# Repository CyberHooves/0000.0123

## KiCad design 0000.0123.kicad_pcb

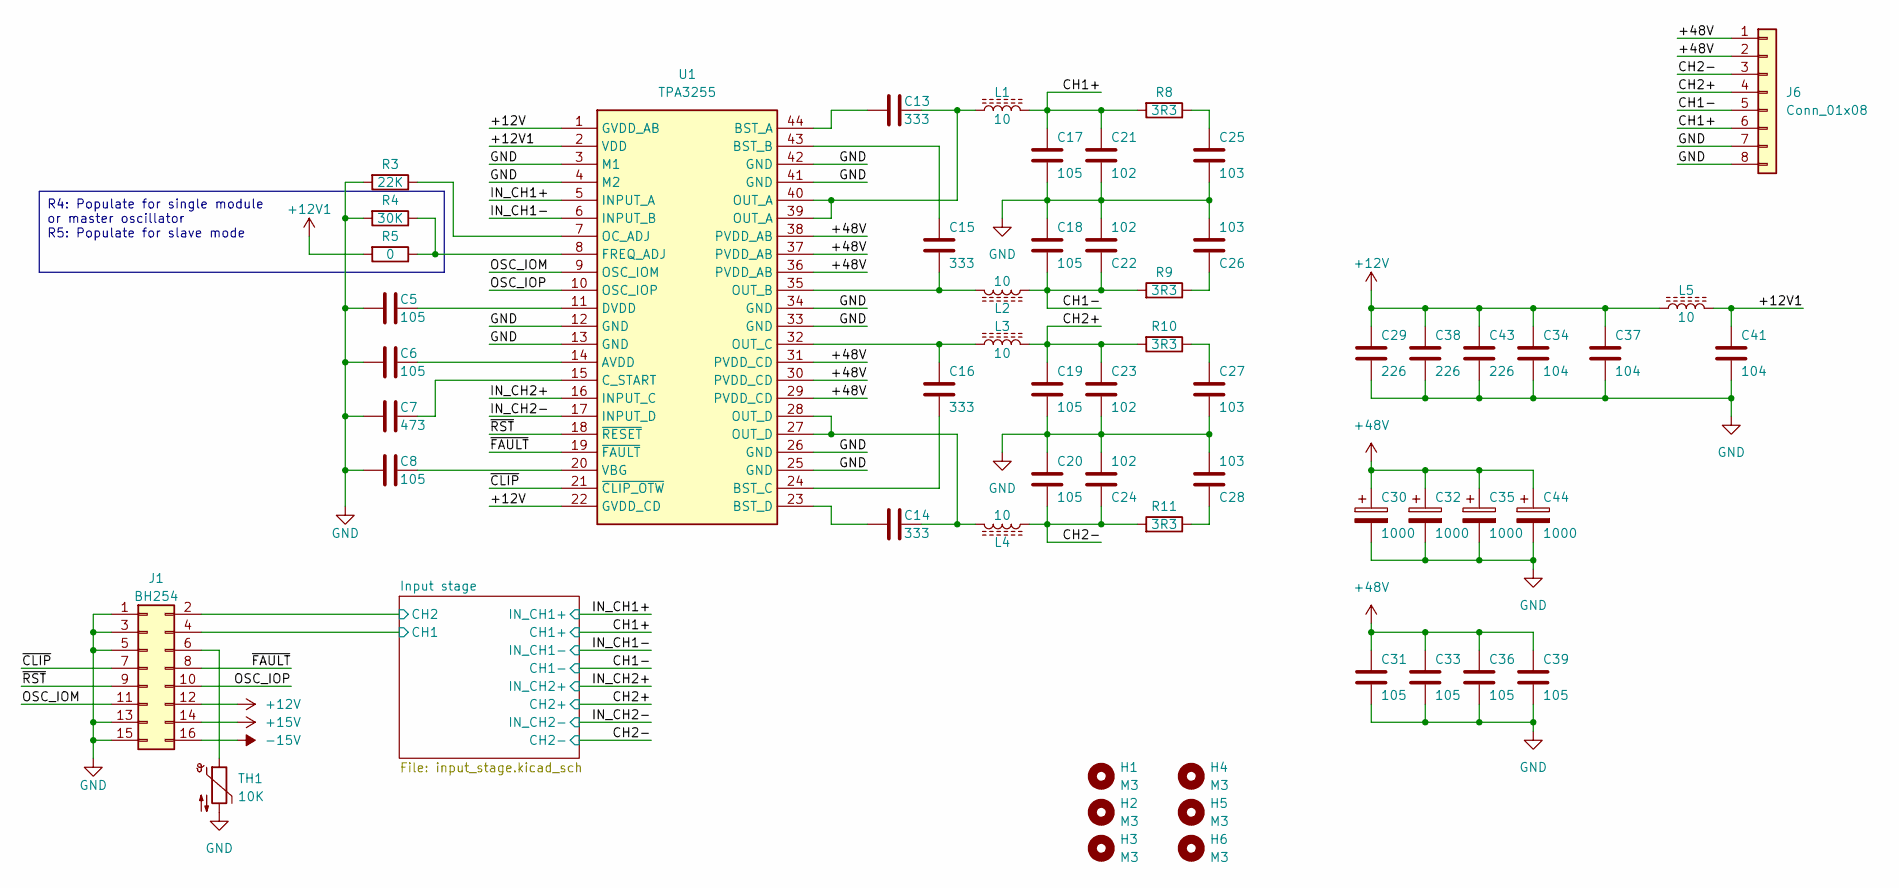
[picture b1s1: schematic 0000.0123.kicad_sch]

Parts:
C5, C6, C8: 105; C_0805_2012Metric
C7: 473; C_0805_2012Metric
C13, C14, C15, C16: 333; C_0805_2012Metric
C17, C18, C19, C20: 105; C_Rect_L18.0mm_W8.0mm_P15.00mm_FKS3_FKP3
C21, C22, C23, C24: 102; C_0805_2012Metric
C25, C26, C27, C28: 103; C_0805_2012Metric
C29, C38, C43: 226; C_1210_3225Metric
C30, C32, C35, C44: 1000; CP_Radial_D16.0mm_P7.50mm
C31, C33, C36, C39: 105; C_1210_3225Metric
C34, C37, C41: 104; C_0805_2012Metric
H1, H2, H3, H4, H5, H6: M3; MountingHole_3.2mm_M3
J1: BH254; IDC-Header_2x08_P2.54mm_Vertical
J6: Conn_01x08; PhoenixContact_MCV_1,5_8-G-5.08_1x08_P5.08mm_Vertical
L1, L2, L3, L4: 10; L_TOROID_D25_W10_P8_V_1
L5: 10; L_1210_3225Metric
R3: 22K; R_0805_2012Metric
R4: 30K; R_0805_2012Metric
R5: 0; R_0805_2012Metric
R8, R9, R10, R11: 3R3; R_0805_2012Metric
TH1: 10K; R_0805_2012Metric
U1: TPA3255; HTSSOP-44_6.1x14mm_P0.635mm_TopEP4.14x7.01mm

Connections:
+12V: C29.1, C34.1, C37.1, C38.1, C43.1, J1.12, L5.1, U1.1 (GVDD_AB), U1.22 (GVDD_CD)
+12V1: C41.1, L5.2, R5.2, U1.2 (VDD)
+15V: J1.14; also elsewhere on the board
+48V: C30.1, C31.1, C32.1, C33.1, C35.1, C36.1, C39.1, C44.1, J6.1, J6.2, U1.29 (PVDD_CD), U1.30 (PVDD_CD), U1.31 (PVDD_CD), U1.36 (PVDD_AB), U1.37 (PVDD_AB), U1.38 (PVDD_AB)
-15V: J1.16; also elsewhere on the board
/CH1+: C17.1, C21.1, J6.6, L1.2, R8.2; also elsewhere on the board
/CH1-: C18.2, C22.1, J6.5, L2.2, R9.2; also elsewhere on the board
/CH2+: C19.1, C23.1, J6.4, L3.2, R10.2; also elsewhere on the board
/CH2-: C20.2, C24.1, J6.3, L4.2, R11.2; also elsewhere on the board
/IN_CH1+: U1.5 (INPUT_A); also elsewhere on the board
/IN_CH1-: U1.6 (INPUT_B); also elsewhere on the board
/IN_CH2+: U1.16 (INPUT_C); also elsewhere on the board
/IN_CH2-: U1.17 (INPUT_D); also elsewhere on the board
/Input stage/CH1: J1.4; also elsewhere on the board
/Input stage/CH2: J1.2; also elsewhere on the board
/OSC_IOM: J1.11, U1.9 (OSC_IOM)
/OSC_IOP: J1.10, U1.10 (OSC_IOP)
/~CLIP: J1.7, U1.21 (~CLIP_OTW)
/~FAULT: J1.8, U1.19 (~FAULT)
/~RST: J1.9, U1.18 (~RESET)
GND: C5.1, C6.1, C7.1, C8.1, C17.2, C18.1, C19.2, C20.1, C21.2, C22.2, C23.2, C24.2, C25.2, C26.2, C27.2, C28.2, C29.2, C30.2, C31.2, C32.2, C33.2, C34.2, C35.2, C36.2, C37.2, C38.2, C39.2, C41.2, C43.2, C44.2, J1.1, J1.3, J1.5, J1.13, J1.15, J6.7, J6.8, R3.2, R4.2, TH1.2, U1.3 (M1), U1.4 (M2), U1.12 (GND), U1.13 (GND), U1.25 (GND), U1.26 (GND), U1.33 (GND), U1.34 (GND), U1.41 (GND), U1.42 (GND); also elsewhere on the board
unnamed: C13.2, L1.1, U1.39 (OUT_A), U1.40 (OUT_A)
unnamed: C14.2, L4.1, U1.27 (OUT_D), U1.28 (OUT_D)
unnamed: C25.1, R8.1
unnamed: C26.1, R9.1
unnamed: C27.1, R10.1
unnamed: C28.1, R11.1
unnamed: J1.6, TH1.1
unnamed: C6.2, U1.14 (AVDD)
unnamed: C13.1, U1.44 (BST_A)
unnamed: C15.1, U1.43 (BST_B)
unnamed: C16.2, U1.24 (BST_C)
unnamed: C14.1, U1.23 (BST_D)
unnamed: C7.2, U1.15 (C_START)
unnamed: C5.2, U1.11 (DVDD)
unnamed: R4.1, R5.1, U1.8 (FREQ_ADJ)
unnamed: R3.1, U1.7 (OC_ADJ)
unnamed: C15.2, L2.1, U1.35 (OUT_B)
unnamed: C16.1, L3.1, U1.32 (OUT_C)
unnamed: C8.2, U1.20 (VBG)

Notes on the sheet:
R4: Populate for single module or master oscillator R5: Populate for slave mode

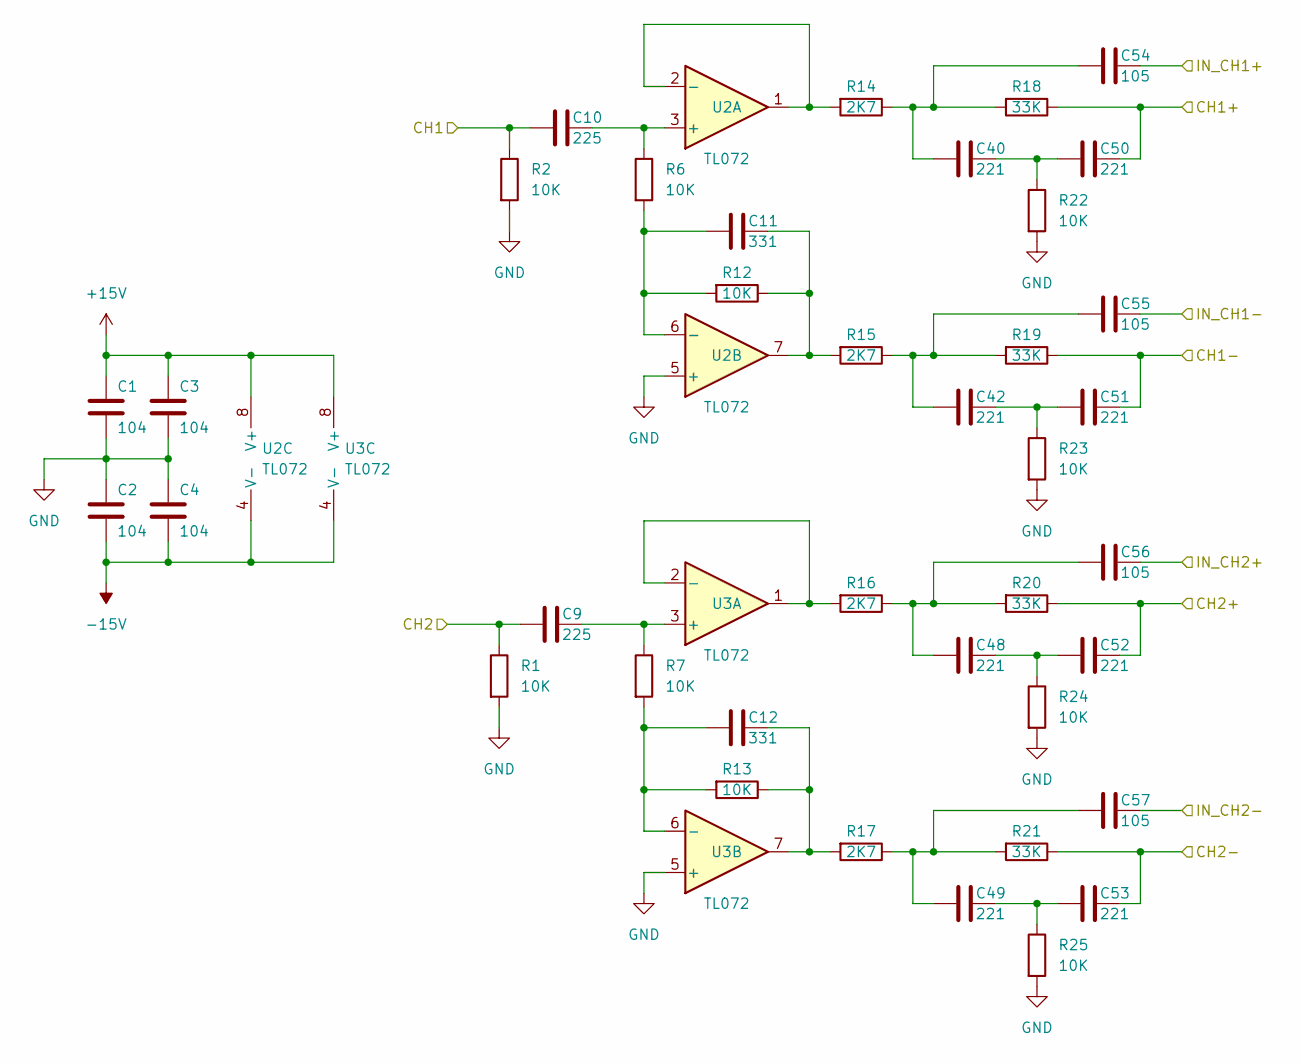
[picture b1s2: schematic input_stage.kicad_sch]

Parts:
C1, C2, C3, C4: 104; C_0805_2012Metric
C9, C10: 225; C_1210_3225Metric
C11, C12: 331; C_0805_2012Metric
C40, C42, C48, C49, C50, C51, C52, C53: 221; C_0805_2012Metric
C54, C55, C56, C57: 105; C_0805_2012Metric
R1, R2, R6, R7, R12, R13, R22, R23, R24, R25: 10K; R_0805_2012Metric
R14, R15, R16, R17: 2K7; R_0805_2012Metric
R18, R19, R20, R21: 33K; R_0805_2012Metric
U2, U3: TL072; SOIC-8_3.9x4.9mm_P1.27mm

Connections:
+15V: C1.1, C3.1, U2.8 (V+), U3.8 (V+); also elsewhere on the board
-15V: C2.2, C4.2, U2.4 (V-), U3.4 (V-); also elsewhere on the board
/CH1+: C50.2, R18.1; also elsewhere on the board
/CH1-: C51.2, R19.1; also elsewhere on the board
/CH2+: C52.2, R20.1; also elsewhere on the board
/CH2-: C53.2, R21.1; also elsewhere on the board
/IN_CH1+: C54.2; also elsewhere on the board
/IN_CH1-: C55.2; also elsewhere on the board
/IN_CH2+: C56.2; also elsewhere on the board
/IN_CH2-: C57.2; also elsewhere on the board
/Input stage/CH1: C10.1, R2.1; also elsewhere on the board
/Input stage/CH2: C9.1, R1.1; also elsewhere on the board
GND: C1.2, C2.1, C3.2, C4.1, R1.2, R2.2, R22.2, R23.2, R24.2, R25.2, U2.5 (+), U3.5 (+); also elsewhere on the board
unnamed: C11.2, R12.1, R15.2, U2.7
unnamed: C12.2, R13.1, R17.2, U3.7
unnamed: C40.1, C54.1, R14.1, R18.2
unnamed: C40.2, C50.1, R22.1
unnamed: C42.1, C55.1, R15.1, R19.2
unnamed: C42.2, C51.1, R23.1
unnamed: C48.1, C56.1, R16.1, R20.2
unnamed: C48.2, C52.1, R24.1
unnamed: C49.1, C57.1, R17.1, R21.2
unnamed: C49.2, C53.1, R25.1
unnamed: C10.2, R6.1, U2.3 (+)
unnamed: R14.2, U2.1, U2.2 (-)
unnamed: C11.1, R6.2, R12.2, U2.6 (-)
unnamed: C9.2, R7.1, U3.3 (+)
unnamed: R16.2, U3.1, U3.2 (-)
unnamed: C12.1, R7.2, R13.2, U3.6 (-)

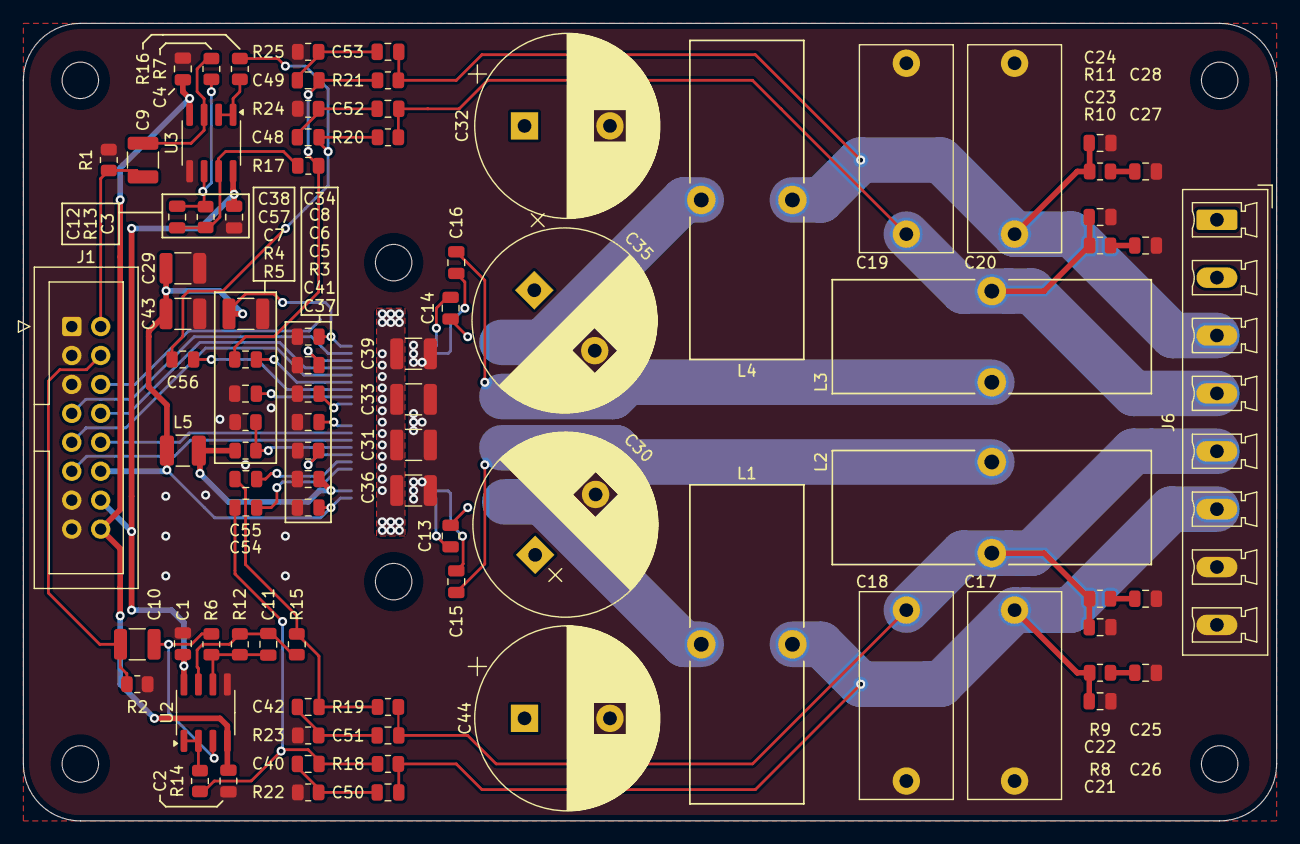
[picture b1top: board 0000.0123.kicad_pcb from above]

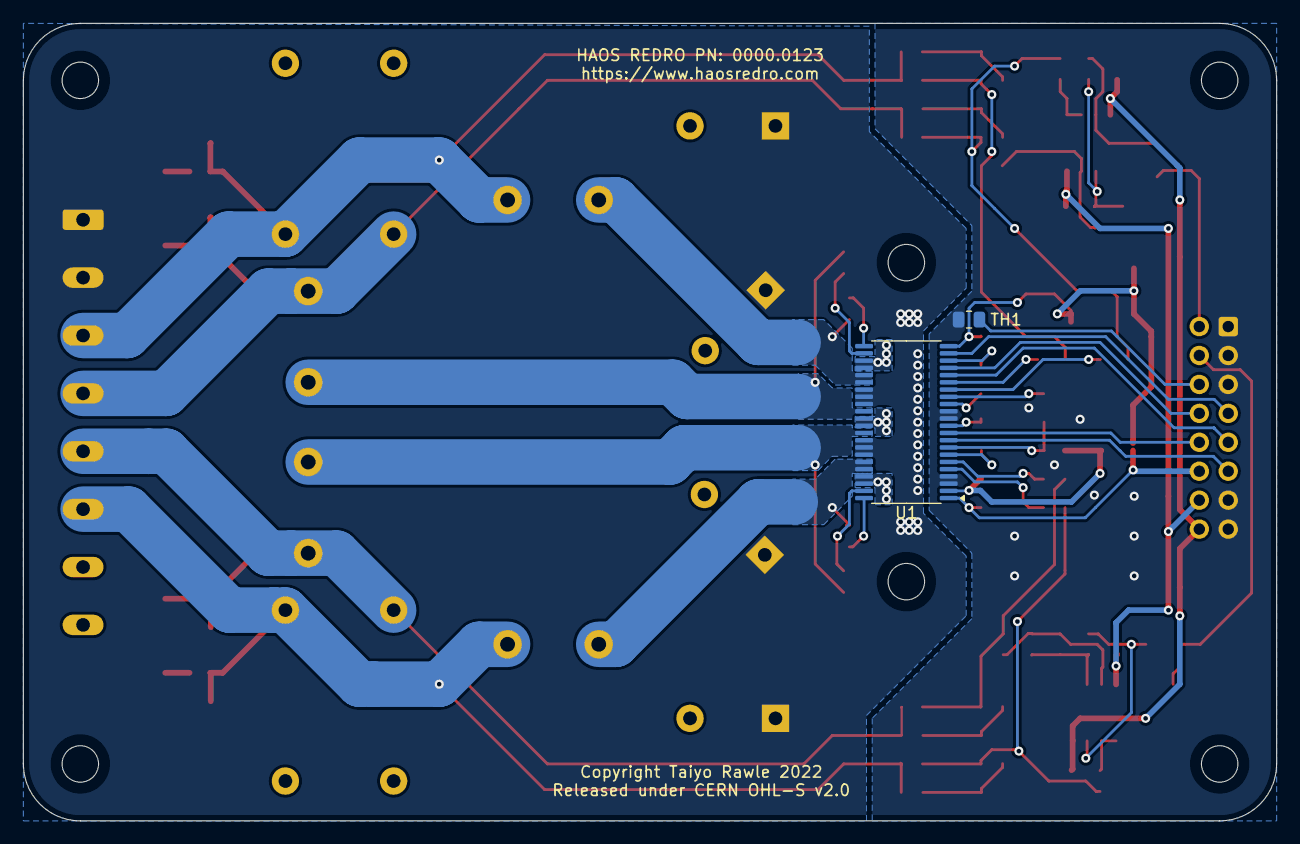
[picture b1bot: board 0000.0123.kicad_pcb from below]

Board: 2 copper layers, 110.0 x 70.0 mm, 96 parts (2 on the bottom side), 56 nets.

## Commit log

2025-06-06 Updated PCB layout.
2025-10-03 Fixed minor error - R5 is now connected to +12V1 instead of +12V.
2025-10-03 Fixed some whoopsies.

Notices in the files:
0000.0123.kicad_pcb:
Copyright Taiyo Rawle 2022
Released under CERN OHL-S v2.0
